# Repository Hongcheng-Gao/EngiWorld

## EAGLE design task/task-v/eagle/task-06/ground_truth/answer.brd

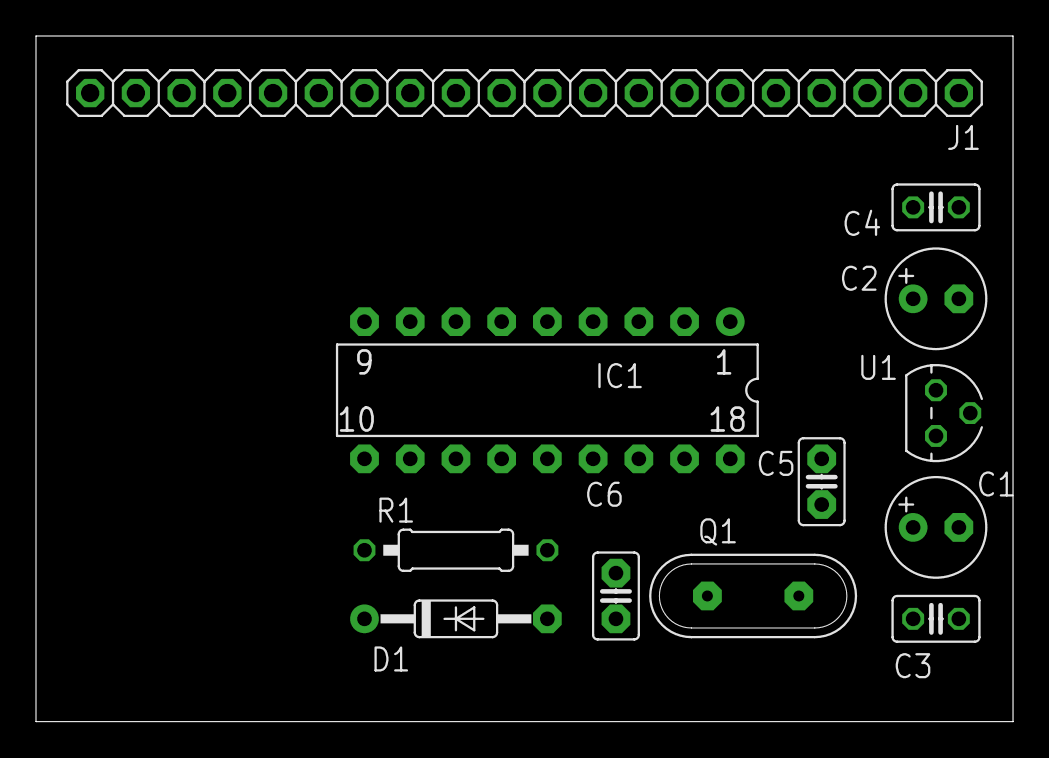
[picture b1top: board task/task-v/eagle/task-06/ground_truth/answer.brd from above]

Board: 2 copper layers, 54.3 x 38.1 mm, 12 parts (0 on the bottom side), 20 nets, no tracks yet.

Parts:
C1, C2: 10u; E2,5-6
C3, C4: 10n; C025-025X050
C5, C6: 27p; C2,5-2
D1: 1N4148; DO35-10
IC1: 16F84; DIL18
J1: 1X20
Q1: QS
R1: 2.2k; 0207/10
U1: 78L05; TO92

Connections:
+12V: C1.+, C3.2, J1.2, U1.3
A0: IC1.17, J1.4
A1: IC1.18, J1.5
A2: IC1.1, J1.6
A3: IC1.2, J1.7
A4: IC1.3, J1.8
B0: IC1.6, J1.9
B1: IC1.7, J1.10
B2: IC1.8, J1.11
B3: IC1.9, J1.12
B4: IC1.10, J1.13
B5: IC1.11, J1.14
B6: IC1.12, J1.15, J1.18
B7: IC1.13, J1.16, J1.17
GND: C1.-, C2.-, C3.1, C4.1, C5.1, C6.1, IC1.5, J1.1, J1.20, U1.2
unnamed: D1.K, IC1.4, J1.19
unnamed: D1.A, R1.1
unnamed: C5.2, IC1.16, Q1.2
unnamed: C6.2, IC1.15, Q1.1
VCC: C2.+, C4.2, IC1.14, J1.3, R1.2, U1.1

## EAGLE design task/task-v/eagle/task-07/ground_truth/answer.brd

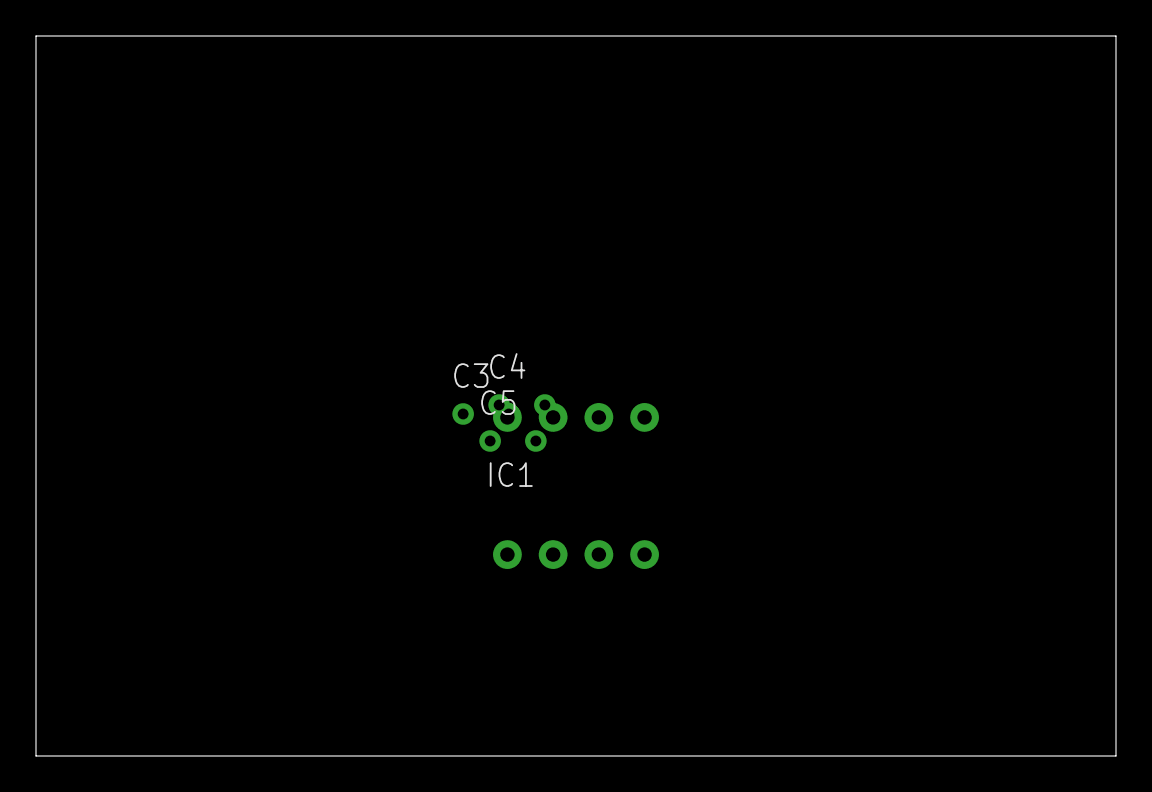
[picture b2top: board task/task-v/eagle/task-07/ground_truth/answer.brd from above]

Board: 1 copper layer, 60.0 x 40.0 mm, 4 parts (0 on the bottom side), 2 nets, no tracks yet.

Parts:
C3, C4, C5: 100n; C025
IC1: GENERIC; DIL8

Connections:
GND: C3.1, C4.1, C5.1, IC1.4
VCC: C3.2, C4.2, C5.2, IC1.8

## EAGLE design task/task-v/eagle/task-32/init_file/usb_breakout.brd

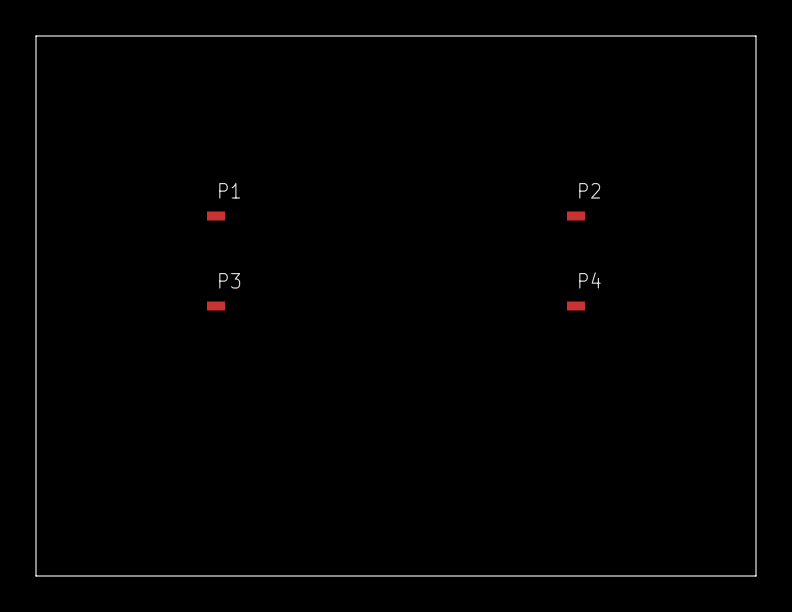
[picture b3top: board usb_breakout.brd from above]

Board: 1 copper layer, 40.0 x 30.0 mm, 4 parts (0 on the bottom side), 2 nets, no tracks yet.

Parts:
P1: USB_DP_A; PAD1
P2: USB_DP_B; PAD1
P3: USB_DM_A; PAD1
P4: USB_DM_B; PAD1

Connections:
USB_DM: P3.1, P4.1
USB_DP: P1.1, P2.1
